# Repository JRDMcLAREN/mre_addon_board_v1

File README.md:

# mre_addon_board_v1

Addon board for microrusEFI ECU.
Wideband controller wiring is based on https://github.com/mck1117/wideband, official rusEFI wideband controller.
This is a version using STM32F042K6Tx MCU in LQFP32 package.

This addon board has build-in rusEFI wideband controller, microSD card slot and K-Thermocouple controller.
It can be used on all MRE with appropriate connector headers.

Wideband controller requires 
* CAN bus connectivity 
* additional power supply from 12V_MREL pin for sensor heater.
(not required for "my" MRE versions - R0.5.5rc, R0.6.1rc)

LSU 4.9 sensor wires are connected via MOLEX MicroFit 3x2 connector 43045-0601 or 43045-0612
K-Thermocouple wires are connected via MOLEX MicroFit 2x1 connector 43045-0202 or 43045-0212

SPI ChipSelect CS# pins:
PA15 - for EGT chip
PB9 - for microSD card

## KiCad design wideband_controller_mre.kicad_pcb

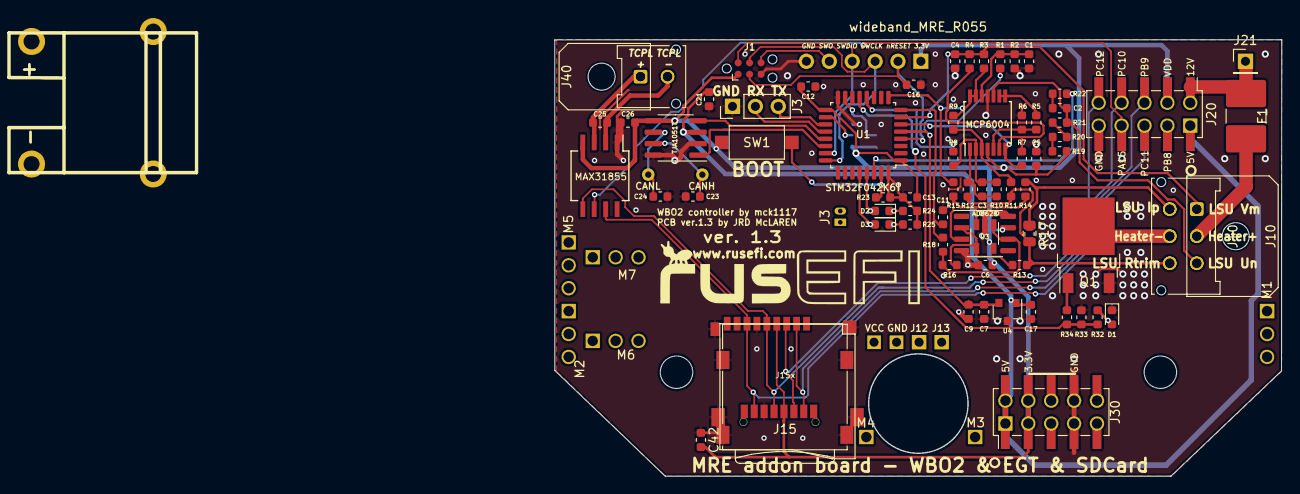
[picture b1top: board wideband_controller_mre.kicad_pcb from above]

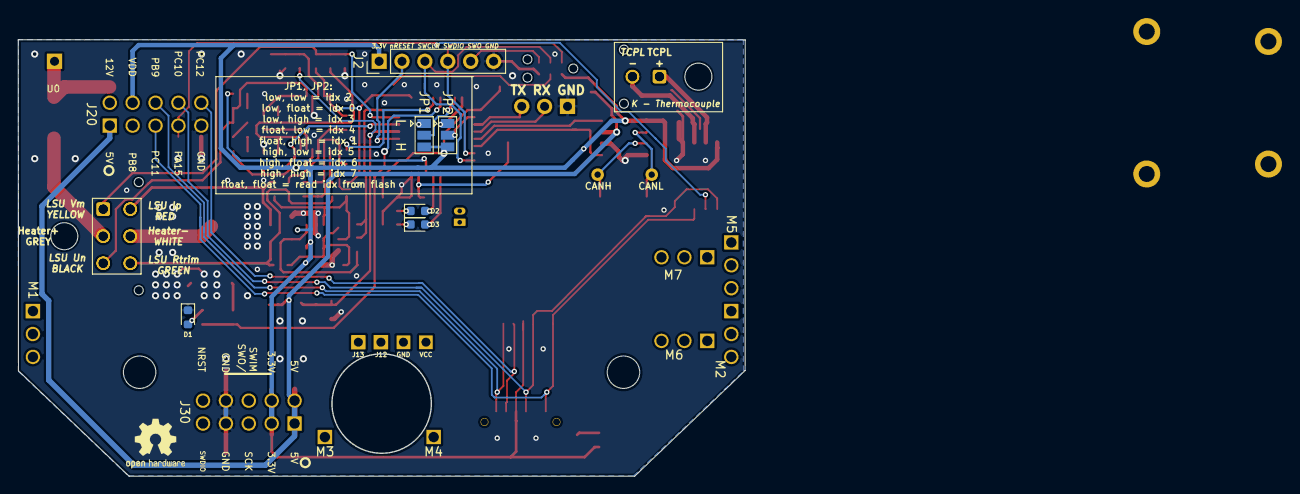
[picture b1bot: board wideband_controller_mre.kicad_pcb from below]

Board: 2 copper layers, 80.6 x 48.4 mm, 81 parts (8 on the bottom side), 61 nets.

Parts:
C1, C4, C7, C16, C17: 1u; C_0603_1608Metric
C2, C5, C6, C9, C11, C12, C13: 100n; C_0603_1608Metric
C3: 33n; C_0603_1608Metric
C21, C26, C42: 100nF; C_0603_1608Metric
C23, C24: 47p; C_0603_1608Metric
C25: 10nF; C_0603_1608Metric
D1, D1#2: RED; LED_0603_1608Metric
D2, D2#2: GREEN; LED_0603_1608Metric
D3, D3#2: BLUE; LED_0603_1608Metric
F1: Polyfuse 2A; R_2816_7142Metric
J1: TC2030; Tag-Connect_TC2030-IDC-NL_2x03_P1.27mm_Vertical
J2: Conn_01x06_Male; PinHeader_1x06_P2.54mm_Vertical
J3: Conn_01x03_Male; PinHeader_1x03_P2.54mm_Vertical
J10: Molex_Micro-Fit_3.0_43045-0612_2x03_P3.00mm_Verti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; Molex_Micro-Fit_3.0_43045-0612_2x03_P3.00mm_Vertical
J10#2: Molex_Micro-Fit_3.0_43045-0601_43045-0612; Molex_Micro-Fit_3.0_43045-0600_2x03_P3.00mm_Horizontal
J15: microSD_HC_Wuerth_693072010801
J15x: MICRO-SDCARD-CONNECTOR-3300060P1
J20, J30: Conn_02x05_Odd_Even-Connector_Generic; PinHeader_2x05_P2.54mm_Vertical_SMD
J21: Soldering PAD for 12V_MREL; PinHeader_1x01_P2.54mm_Vertical
J40: CONN_Molex; Molex_Micro-Fit_3.0_43045-0200_2x01_P3.00mm_Horizontal
J40x: Molex_Micro-Fit_3.0_43045-0212_2x01_P3.00mm_Verti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; Molex_Micro-Fit_3.0_43045-0212_2x01_P3.00mm_Vertical
J41: CONN_Sparkfun; tcpl_PCC-SMP
JP1, JP2: Jumper_3_Open; SolderJumper-3_P1.3mm_Open_Pad1.0x1.5mm
LOGO1: DNP; OSHW-Logo2_7.3x6mm_SilkScreen
Q1: BTS3028; TO-252-2
R1, R2, R24, R25, R32, R33, R34: 1k; R_0603_1608Metric
R3: 10; R_0603_1608Metric
R4, R5, R10, R11, R13, R14, R23: 10k; R_0603_1608Metric
R6, R7: 27k; R_0603_1608Metric
R8, R9: 68k; R_0603_1608Metric
R12: 47; R_0603_1608Metric
R15, R16: 100k; R_0603_1608Metric
R17: 61.9; R_0805_2012Metric
R17#2: 61.9; R_0603_1608Metric
R18: 3.3k; R_0603_1608Metric
R19, R20, R21: 20k; R_0603_1608Metric
R22: 22k; R_0603_1608Metric
SW1: SW_Push; SW_SPST_CK_RS282G05A3
U0: wideband_MRE_R055
U1: STM32F042K6Tx; LQFP-32_7x7mm_P0.8mm
U2: MCP6004; TSSOP-14_4.4x5mm_P0.65mm
U3: AD8628; SO-8_3.9x4.9mm_P1.27mm
U3#2: AD8628; TSOT-23-5
U4: REF3033; SOT-23
U5: TJA1051T-3; SOIC-8_3.9x4.9mm_P1.27mm
U6: MAX31855KASA; SO-8_5.3x6.2mm_P1.27mm

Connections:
+3.3V: C5.1, C6.1, C12.1, C13.1, C26.1, C42.2, J1.1, J2.1, J15.4, J15x.4, J20.3, J30.3, J30.4, JP1.3, JP2.3, R19.2, SW1.1, U0.J203, U0.J204, U0.J804, U1.1, U1.17, U2.4, U3.7, U3#2.5, U5.5, U6.4
+5V: C17.1, C21.2, J20.2, J30.1, J30.2, U0.J201, U0.J202, U0.J801, U4.1, U5.3
/can_fet_conn_mre_wbo2/12V_MREL: F1.1, J20.1, J21.1, U0.J802
/can_fet_conn_mre_wbo2/CAN_H: C23.2, U0.J49, U5.7
/can_fet_conn_mre_wbo2/CAN_L: C24.1, U0.J50, U5.6
/can_fet_conn_mre_wbo2/LSU_Heater+: F1.2, J10.2, J10#2.2
/can_fet_conn_mre_wbo2/LSU_Heater-: J10.5, J10#2.5, Q1.2
/can_fet_conn_mre_wbo2/NRST: J30.10, U0.J210
/can_fet_conn_mre_wbo2/PA15: J20.8, U0.J807, U6.6
/can_fet_conn_mre_wbo2/PB8: J20.4, U0.J803
/can_fet_conn_mre_wbo2/PB9: J15.2, J15x.2, J20.5, U0.J806
/can_fet_conn_mre_wbo2/PC10: J15.5, J15x.5, J20.7, U0.J808, U6.5
/can_fet_conn_mre_wbo2/PC11: J15.7, J15x.7, J20.6, U0.J805, U6.7
/can_fet_conn_mre_wbo2/PC12: J15.3, J15x.3, J20.9, U0.J810
/can_fet_conn_mre_wbo2/SCK: J30.5, U0.J205
/can_fet_conn_mre_wbo2/SWDIO: J30.9, U0.J209
/can_fet_conn_mre_wbo2/SWIM: J30.6, U0.J206
/can_fet_conn_mre_wbo2/TCPL+: C25.1, J40.1, J40x.1, J41.2, U6.3
/can_fet_conn_mre_wbo2/TCPL-: C25.2, J40.2, J40x.2, J41.1, U6.2
/mcu_adc_mre_wbo2/Boot0: R23.2, SW1.2, U1.31
/mcu_adc_mre_wbo2/Ip_dac: R8.1, U1.12
/mcu_adc_mre_wbo2/Ip_sense: C11.1, R18.2, U1.8
/mcu_adc_mre_wbo2/LED_BLUE: D3.2, D3#2.2, U1.28
/mcu_adc_mre_wbo2/LED_GREEN: D2.2, D2#2.2, U1.29
/mcu_adc_mre_wbo2/LSU_Un_sense: R5.1, U2.8, U2.9
/mcu_adc_mre_wbo2/Nernst_esr_drive: R22.2, U1.30
/mcu_adc_mre_wbo2/SEL_1: JP1.2, U1.15
/mcu_adc_mre_wbo2/SEL_2: JP2.2, U1.18
/mcu_adc_mre_wbo2/SWCLK: J1.4, J2.3, U1.24
/mcu_adc_mre_wbo2/SWDIO: J1.2, J2.4, U1.23
/mcu_adc_mre_wbo2/SWO: J1.6, J2.5
/mcu_adc_mre_wbo2/UART_RX: J3.2, U1.20
/mcu_adc_mre_wbo2/UART_TX: J3.3, U1.19
/mcu_adc_mre_wbo2/Un_sense: R7.2, U1.6, U2.7
/mcu_adc_mre_wbo2/Vm: R3.2, R9.2, R15.2, U1.9, U2.13, U2.14
/mcu_adc_mre_wbo2/nRESET: C16.1, J1.3, J2.2, U1.4
CAN_RX: U1.21, U5.4
CAN_TX: U1.22, U5.1
GND: C1.2, C4.2, C5.2, C6.2, C7.2, C9.2, C11.2, C12.2, C13.2, C16.2, C17.2, C21.1, C23.1, C24.2, C26.2, C42.1, D1.1, D1#2.1, J1.5, J2.6, J3.1, J15.6, J15.9, J15x.6, J15x.G1, J15x.G2, J15x.G3, J15x.G4, J20.10, J30.7, J30.8, JP1.1, JP2.1, Q1.3, R2.2, R6.2, R23.1, R24.1, R25.1, R33.1, U0.J207, U0.J208, U0.J809, U1.16, U1.32, U2.11, U3.4, U3.8, U3#2.2, U4.3, U5.2, U5.8, U6.1
LSU_Ip: J10.4, J10#2.4, R14.2, R17.2, R17#2.2
LSU_Rtrim: J10.6, J10#2.6, R11.1, R12.1, R13.2, R17.1, R17#2.1
LSU_Un: C2.1, J10.3, J10#2.3, R21.1, U2.10
LSU_Vm: C4.1, J10.1, J10#2.1, R3.1, R4.1, U1.7
unnamed: C1.1, R1.2, R2.1, U2.12
unnamed: C2.2, R22.1
unnamed: C3.1, R10.1, R12.2, U2.1
unnamed: C3.2, R8.2, R10.2, U2.2
unnamed: D1.2, D1#2.2, R32.1
unnamed: D2.1, D2#2.1, R24.2
unnamed: D3.1, D3#2.1, R25.2
unnamed: Q1.1, R34.1
unnamed: R4.2, R7.1, U2.6
unnamed: R5.2, R6.1, U2.5
unnamed: R9.1, R11.2, U2.3
unnamed: R13.1, R16.2, U3.2, U3#2.4
unnamed: R14.1, R15.1, U3.3, U3#2.3
unnamed: R16.1, R18.1, U3.6, U3#2.1
unnamed: R19.1, R20.2
unnamed: R20.1, R21.2
VDDA: C7.1, C9.1, R1.1, U1.5, U4.2
heater_pwm: R32.2, R33.2, R34.2, U1.13
